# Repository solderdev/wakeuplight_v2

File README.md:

# wakeuplight_v2
ESP32 LED-strip wakeuplight with audio stream, NTP, etc.

Second version of my wakeuplight.

Uses an ESP32, N-channel MOSFETs with gate-drivers PWM-controlling multiple warm-white 24V-LED-strips.

Additionally an internet radio may wake you up.

Time is synchronized via NTP.

## Features

* PWA webinterface for easy control and live-feedback
* manually activate light and regulate intensity
* set fade start time and duration
* over-complicated fade algorithm for added smoothness
* store multiple WiFi credentials and connect / reconnect
* NTP time sync
* sunrise / sunset calculation and default intesity regulation
* store settings in NVM
* logging to serial out

## Build / run

* Build using PlatformIO
* F1 -> Tasks: Run task -> PlatformIO: Build filesystem image (esp32dev)
* F1 -> Tasks: Run task -> PlatformIO: Upload filesystem image (esp32dev)
* run program:
* PlatformIO: Build
* PlatformIO: Upload and Monitor

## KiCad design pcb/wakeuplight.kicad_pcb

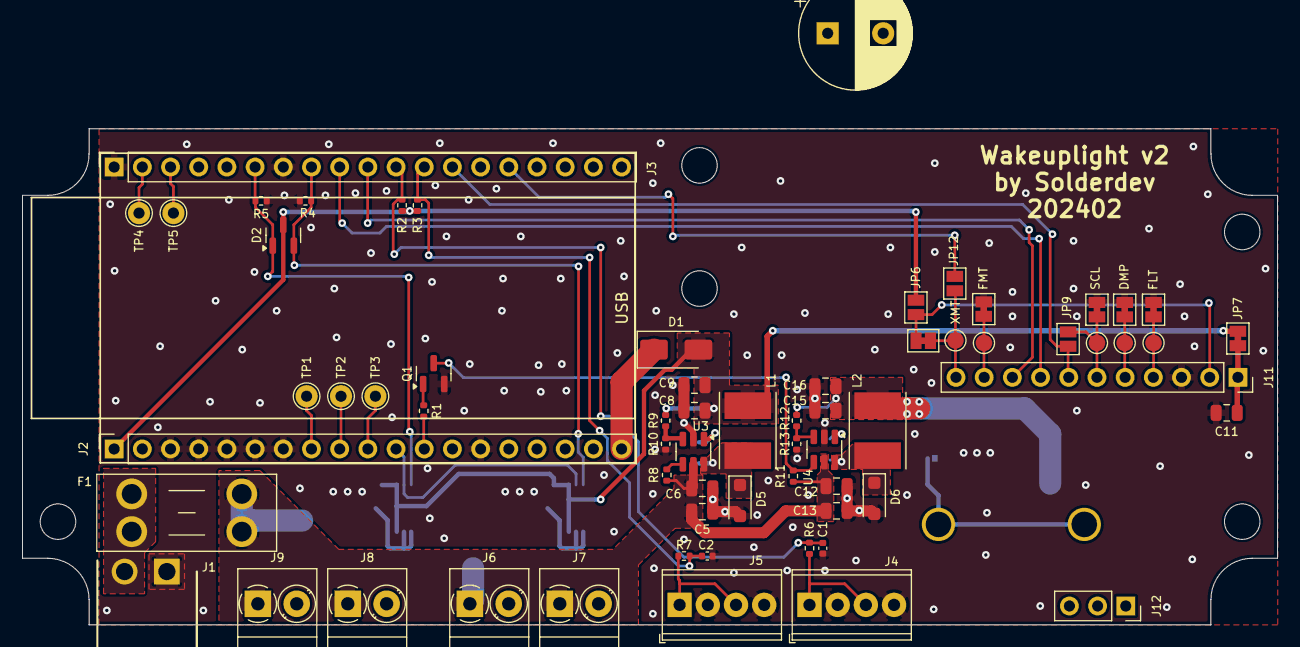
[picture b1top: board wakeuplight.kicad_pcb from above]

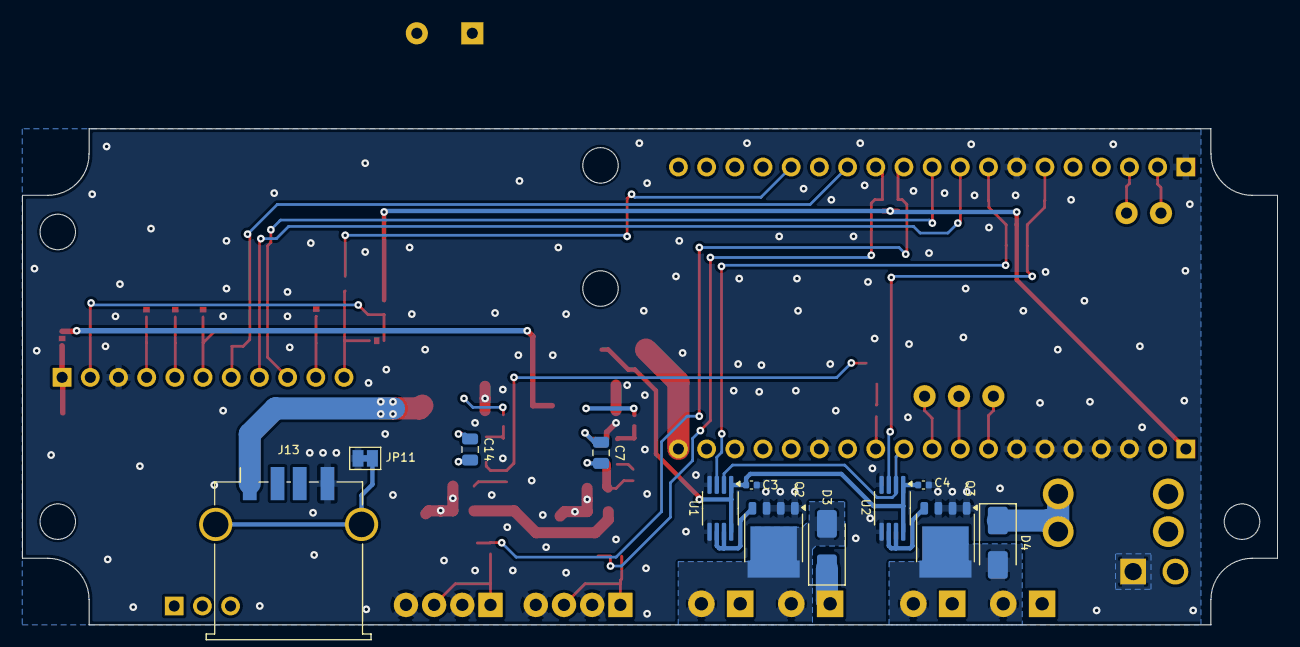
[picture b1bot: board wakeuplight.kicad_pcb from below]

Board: 2 copper layers, 113.1 x 44.7 mm, 82 parts (12 on the bottom side), 45 nets.

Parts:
C1, C2, C3, C4: 1uF 10V; C_0402_1005Metric
C5, C6, C12, C13: 1uF 35V; C_0805_2012Metric
C7, C14: 100nF 50V; C_0805_2012Metric
C8, C9, C11, C15, C16: 10uF 10V; C_0805_2012Metric
C17: ? uF; CP_Radial_D10.0mm_P5.00mm
D1, D3, D4: SS16_R2_00001 1A, 42V; D_SMA
D2: BAT54C; SOT-23
D5, D6: PMEG2020EH; D_SOD-123F
F1: Keystone_3568; Fuseholder_Blade_Mini_Keystone_3568
H1, H2, H3, H4, H7: MountingHole; MountingHole_3.2mm_M3_DIN965
J1: 691322310002; Wuerth_Term_3.81_1x2_691322310002
J2, J3: Conn_01x19; PinSocket_1x19_P2.54mm_Vertical
J4, J5: MPT 2,54; TerminalBlock_Phoenix_MPT-0,5-4-2.54_1x04_P2.54mm_Horizontal
J6, J7, J8, J9: MKDS 3.5mm; TerminalBlock_Phoenix_PT-1,5-2-3.5-H_1x02_P3.50mm_Horizontal
J11: PCM5102A Breakout; PinSocket_1x11_P2.54mm_Vertical
J12: Conn_01x03_Pin; PinSocket_1x03_P2.54mm_Vertical
J13: USB_A; USB_A_TE_292303-7_Horizontal
JP3, JP4, JP5, JP7, JP8, JP10, JP11: SolderJumper_2_Bridged; SolderJumper-2_P1.3mm_Bridged_Pad1.0x1.5mm
JP6, JP9, JP12: SolderJumper_2_Open; SolderJumper-2_P1.3mm_Open_Pad1.0x1.5mm
L1, L2: 22uH SRN5040-220M; L_Taiyo-Yuden_NR-50xx_HandSoldering
Q1: T2N7002BK; SOT-23
Q2, Q3: PSMN1R2-30YLC; LFPAK56
R1, R6, R7: 1k; R_0402_1005Metric
R2, R3: 100k; R_0402_1005Metric
R4, R5, R10, R13: 10k; R_0402_1005Metric
R8, R11: 200k; R_0402_1005Metric
R9, R12: 54k9; R_0402_1005Metric
TP1, TP2, TP3, TP4, TP5: TestPoint; TestPoint_THTPad_D2.0mm_Drill1.0mm
TP6, TP7, TP8, TP9, TP10: TestPoint; TestPoint_Pad_D1.5mm
U1, U2: MCP14A0302; MSOP-8_3x3mm_P0.65mm
U3, U4: LMR16006YQ; SOT-23-6

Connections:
+3V3: D2.3, J2.1, JP6.1 (A), R2.2, R3.2
+5V: C3.1, C4.1, C8.1, C9.1, D1.2 (A), JP7.1 (A), L1.2, R9.1, U1.1 (VDD), U1.8 (VDD), U2.1 (VDD), U2.8 (VDD)
+24V: C5.1, C6.1, C12.1, C13.1, C17.1, D3.1 (K), D4.1 (K), F1.2, J6.1, J7.1, J8.1, J9.1, R8.1, R11.1, U3.5 (VIN), U4.5 (VIN)
/5V_audio: C15.1, C16.1, J13.1 (VBUS), L2.2, R12.1
/EN_bottom: D2.1, J3.6, R5.2, U2.3 (EN)
/EN_top: D2.2, J3.8, R4.2, U1.3 (EN)
/I2S_BCLK: J3.13, J11.7, JP9.2 (B)
/I2S_DOUT: J3.9, J11.8
/I2S_WS: J3.10, J11.9
/PCM5102A/DMP: J11.5, JP4.2 (B), TP7.1
/PCM5102A/FLT: J11.4, JP3.2 (B), TP6.1
/PCM5102A/FMT: J11.10, JP10.2 (B), TP10.1
/PCM5102A/PCM_3V3: J11.2, JP6.2 (B), JP8.1 (A)
/PCM5102A/PCM_5V: C11.1, J11.1, JP7.2 (B)
/PCM5102A/SCL: J11.6, JP5.2 (B), JP9.1 (A), TP8.1
/PCM5102A/XMT: J11.11, JP8.2 (B), JP12.2 (B), TP9.1
/PWM_sig: J2.11, U1.2 (IN), U2.2 (IN)
/button_1: C1.1, J3.11, R2.1, R6.1
/button_2: C2.1, J3.12, R3.1, R7.1
/mute: J3.15, JP12.1 (A)
/regulator_5v/~SHDN: R8.2, U3.4 (~SHDN)
/regulator_5v_audio/~SHDN: Q1.3 (D), R11.2, U4.4 (~SHDN)
/~EN_audio: J2.12, R1.2
GND: C1.2, C2.2, C3.2, C4.2, C5.2, C6.2, C8.2, C9.2, C11.2, C12.2, C13.2, C15.2, C16.2, C17.2, D5.2 (A), D6.2 (A), J1.1, J2.3, J2.4, J2.5, J2.6, J2.7, J2.14, J3.1, J3.7, J4.2, J4.4, J5.2, J5.4, J11.3, J13.4 (GND), JP3.1 (A), JP4.1 (A), JP5.1 (A), JP10.1 (A), JP11.2 (B), Q1.2 (S), Q2.1 (S), Q2.2 (S), Q2.3 (S), Q3.1 (S), Q3.2 (S), Q3.3 (S), R4.1, R5.1, R10.2, R13.2, U1.4 (GND), U1.5 (GND), U2.4 (GND), U2.5 (GND), U3.2 (GND), U4.2 (GND)
unnamed: D1.1 (K), J2.19
unnamed: D3.2 (A), J6.2, J7.2, Q2.5 (D)
unnamed: D4.2 (A), J8.2, J9.2, Q3.5 (D)
unnamed: C7.2, D5.1 (K), L1.1, U3.6 (SW)
unnamed: C14.2, D6.1 (K), L2.1, U4.6 (SW)
unnamed: F1.1, J1.2
unnamed: J2.8, TP1.1
unnamed: J2.9, TP2.1
unnamed: J2.10, TP3.1
unnamed: J3.2, TP4.1
unnamed: J3.3, TP5.1
unnamed: J4.1, J4.3, R6.2
unnamed: J5.1, J5.3, R7.2
unnamed: J13.5 (Shield), JP11.1 (A)
unnamed: Q1.1 (G), R1.1
unnamed: Q2.4 (G), U1.6 (OUT), U1.7 (OUT)
unnamed: Q3.4 (G), U2.6 (OUT), U2.7 (OUT)
unnamed: C7.1, U3.1 (CB)
unnamed: R9.2, R10.1, U3.3 (FB)
unnamed: C14.1, U4.1 (CB)
unnamed: R12.2, R13.1, U4.3 (FB)

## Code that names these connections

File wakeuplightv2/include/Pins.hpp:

#pragma once

#include <Arduino.h>

class Pins
{
public:
  static constexpr uint32_t pwm1 = 27;
  static constexpr uint32_t en_bottom = 21;
  static constexpr uint32_t en_top = 19;
  static constexpr uint32_t button_1 = 17;
  static constexpr uint32_t button_2 = 16;
  static constexpr uint32_t disable_audio_pwr = 14;
  static constexpr uint32_t i2s_dout = 18;
  static constexpr uint32_t i2s_bclk = 4;
  static constexpr uint32_t i2s_lrc = 5;
};

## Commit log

2023-08-15 added git files
2024-01-08 work on pcb
2024-01-21 work on PCB: line out + power done ; removed amplifier from board
2024-02-02 PCB done
2024-02-04 added draft of case design
2024-02-23 case: fixed cutouts for audio module ; added middle PCB standoff
2024-02-23 imported code from wakeuplight v1 ; adopted pins
2024-02-26 added FET-driver enable pins for basic operation
2024-02-27 included schreibfaul1/ESP32-audioI2S library and fought to squeeze it in ROM
2024-02-28 PCB: renamed "EN_audio" to "~EN_audio" ; added input capacitor (PSU noise) ; fixed mirrored MOSFET
2024-03-11 case: modified text on top
2024-03-11 changed LED parameters
2024-03-11 added case for cherry-mx switch
2024-09-12 moved to Kicad 8
